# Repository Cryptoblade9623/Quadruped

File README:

I am making a quadruped using 8 MG90S serovs, an ESP32-C3-Super-Mini and a PCA9685 Servo Driver Board.
I started this project because I like making things and this also coincides with my school robotics club.
This is a way of proving myself, gaining experience and making fun stuff as well.

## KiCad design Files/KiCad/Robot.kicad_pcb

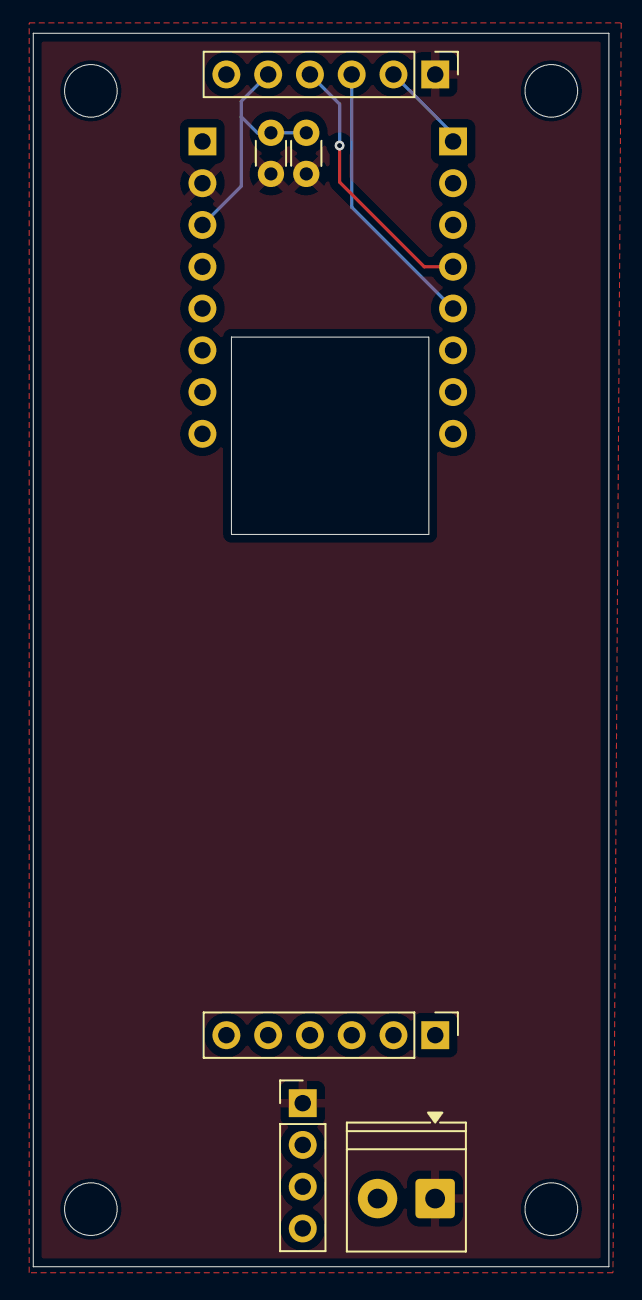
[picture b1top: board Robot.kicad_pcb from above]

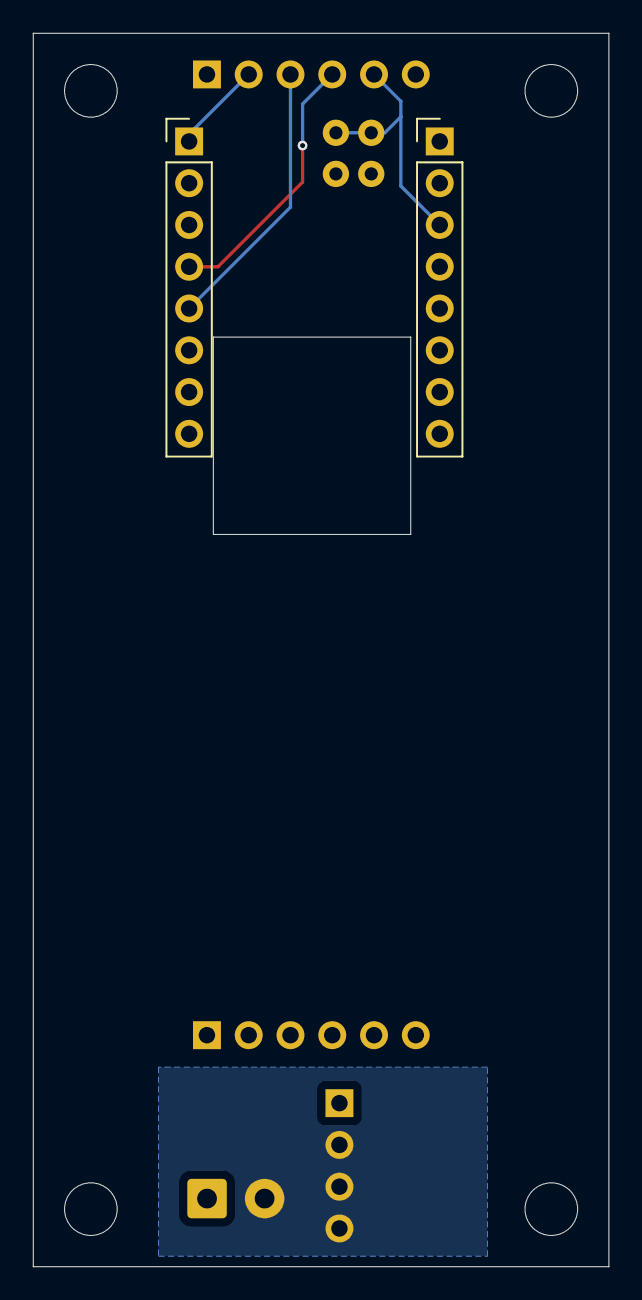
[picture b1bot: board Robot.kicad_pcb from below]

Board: 2 copper layers, 35.0 x 75.0 mm, 8 parts (2 on the bottom side), 6 nets.

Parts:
C1, C2: 0.1u; C_Disc_D3.0mm_W1.6mm_P2.50mm
J1, J6: Conn_01x06_Pin; PinHeader_1x06_P2.54mm_Vertical
J2, J3: Conn_01x08_Pin; PinHeader_1x08_P2.54mm_Vertical
PWR1: Conn_01x02_Pin; TerminalBlock_Phoenix_PT-1,5-2-3.5-H_1x02_P3.50mm_Horizontal
UBin1: Conn_01x04_Pin; PinHeader_1x04_P2.54mm_Vertical

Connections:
GND: C1.1, C2.1, J1.1, J3.2, PWR1.1, UBin1.1
unnamed: J1.2, J2.1
unnamed: J1.3, J2.5
unnamed: J1.4, J2.4
unnamed: C1.2, C2.2, J1.5, J3.3
unnamed: PWR1.2, UBin1.2, UBin1.3, UBin1.4

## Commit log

2026-06-06 Create gsfgo
2026-06-06 Create dfg
2026-06-06 Create g
2026-06-06 Create j
